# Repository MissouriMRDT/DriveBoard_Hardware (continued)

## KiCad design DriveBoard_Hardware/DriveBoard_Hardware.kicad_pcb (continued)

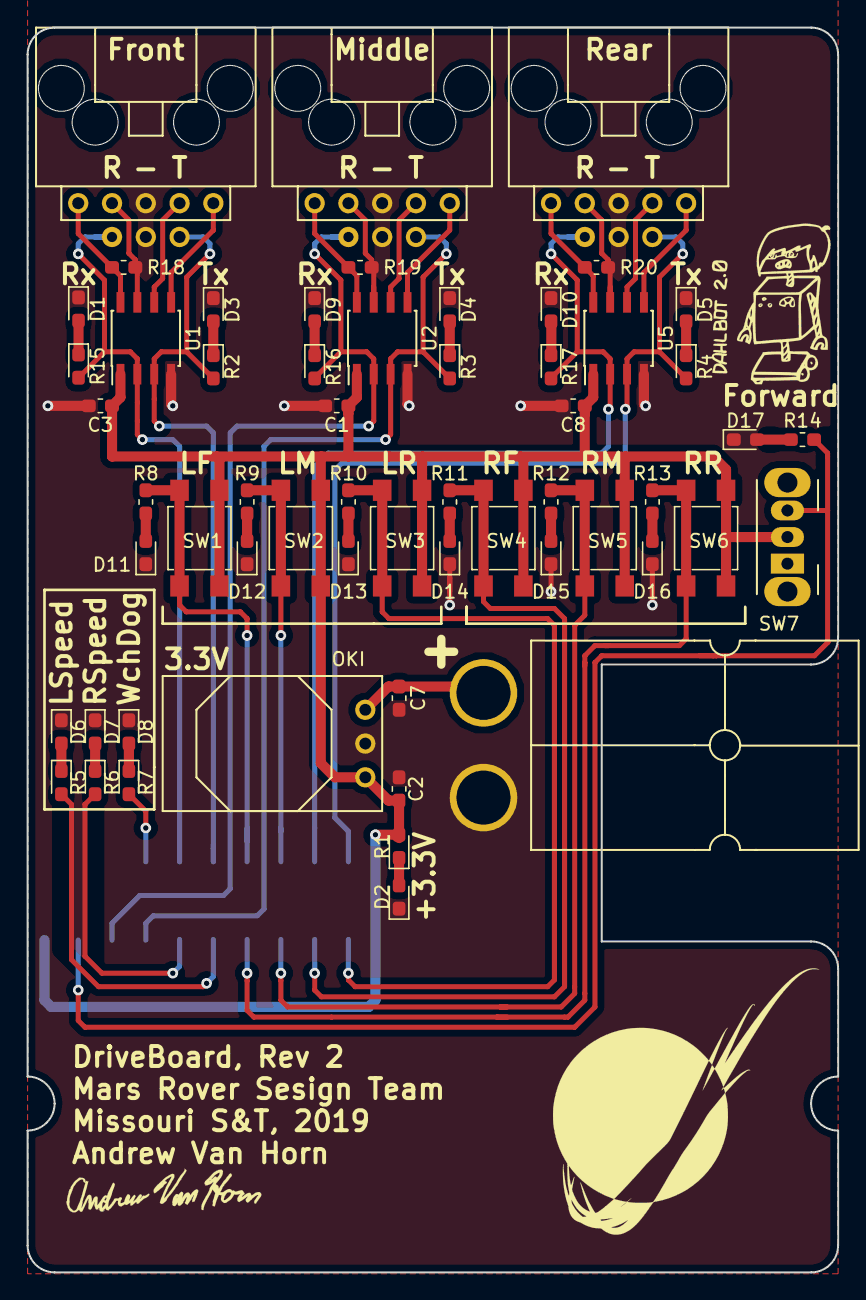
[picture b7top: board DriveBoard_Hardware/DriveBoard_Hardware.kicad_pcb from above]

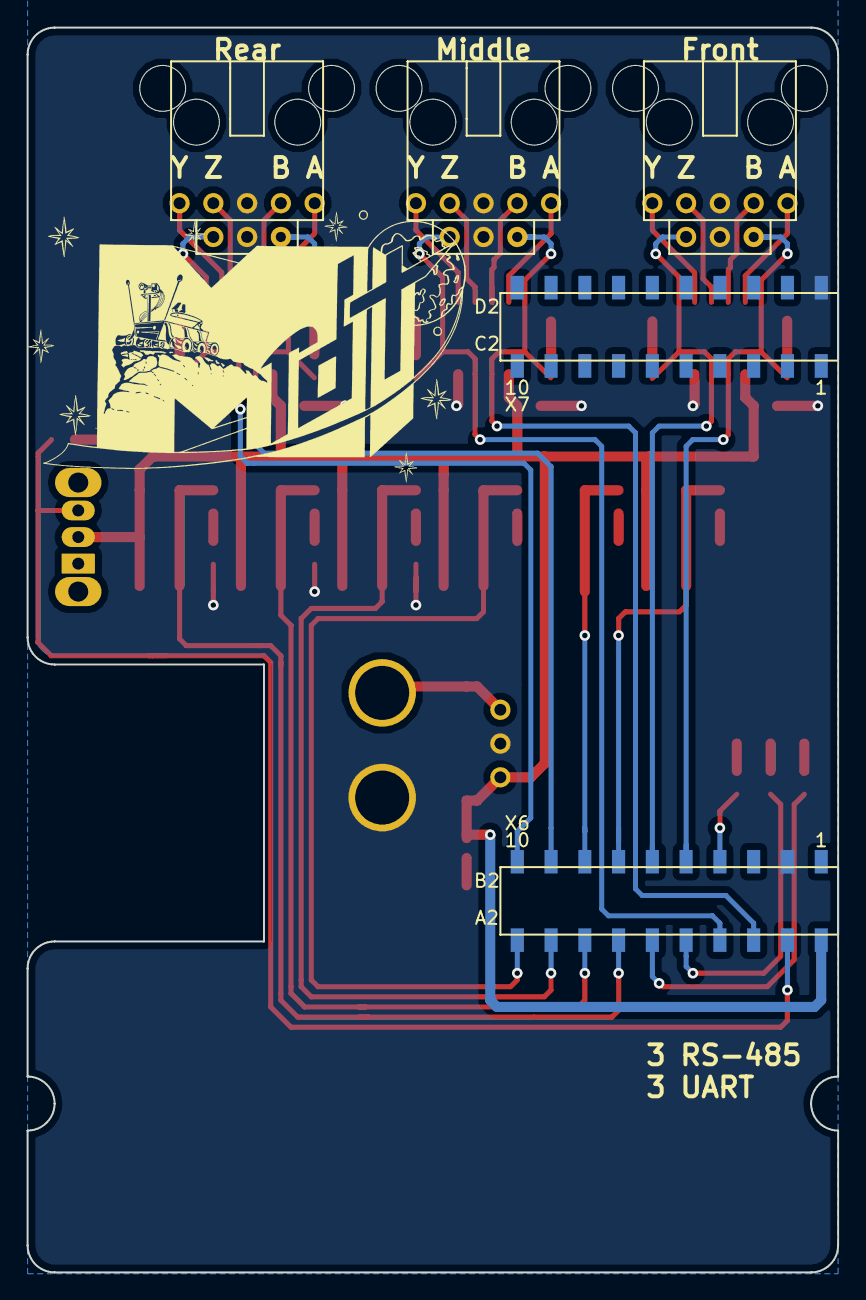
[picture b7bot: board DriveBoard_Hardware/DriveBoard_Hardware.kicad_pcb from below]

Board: 2 copper layers, 61.0 x 93.6 mm, 61 parts (3 on the bottom side), 48 nets.

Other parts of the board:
R18, R19, R20: 120; R_0603_1608Metric_Pad1.05x0.95mm_HandSolder

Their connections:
A1: R18.1; also elsewhere on the board
A2: R19.1; also elsewhere on the board
A3: R20.1; also elsewhere on the board
B1: R18.2; also elsewhere on the board
B2: R19.2; also elsewhere on the board
B3: R20.2; also elsewhere on the board

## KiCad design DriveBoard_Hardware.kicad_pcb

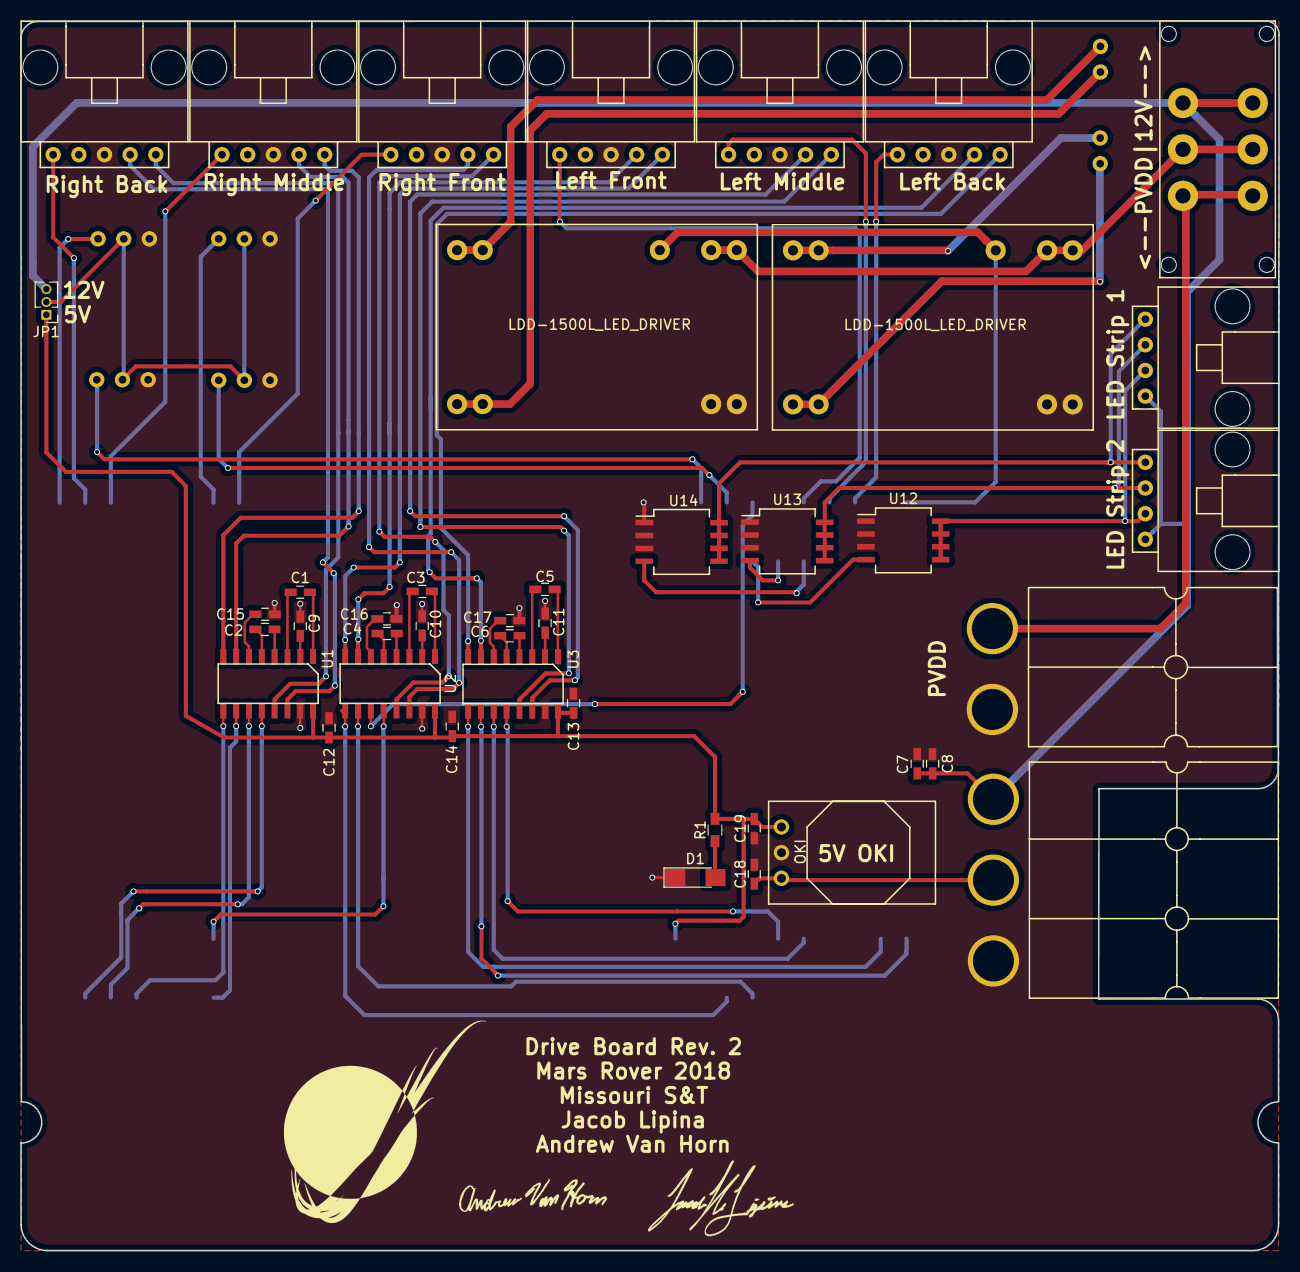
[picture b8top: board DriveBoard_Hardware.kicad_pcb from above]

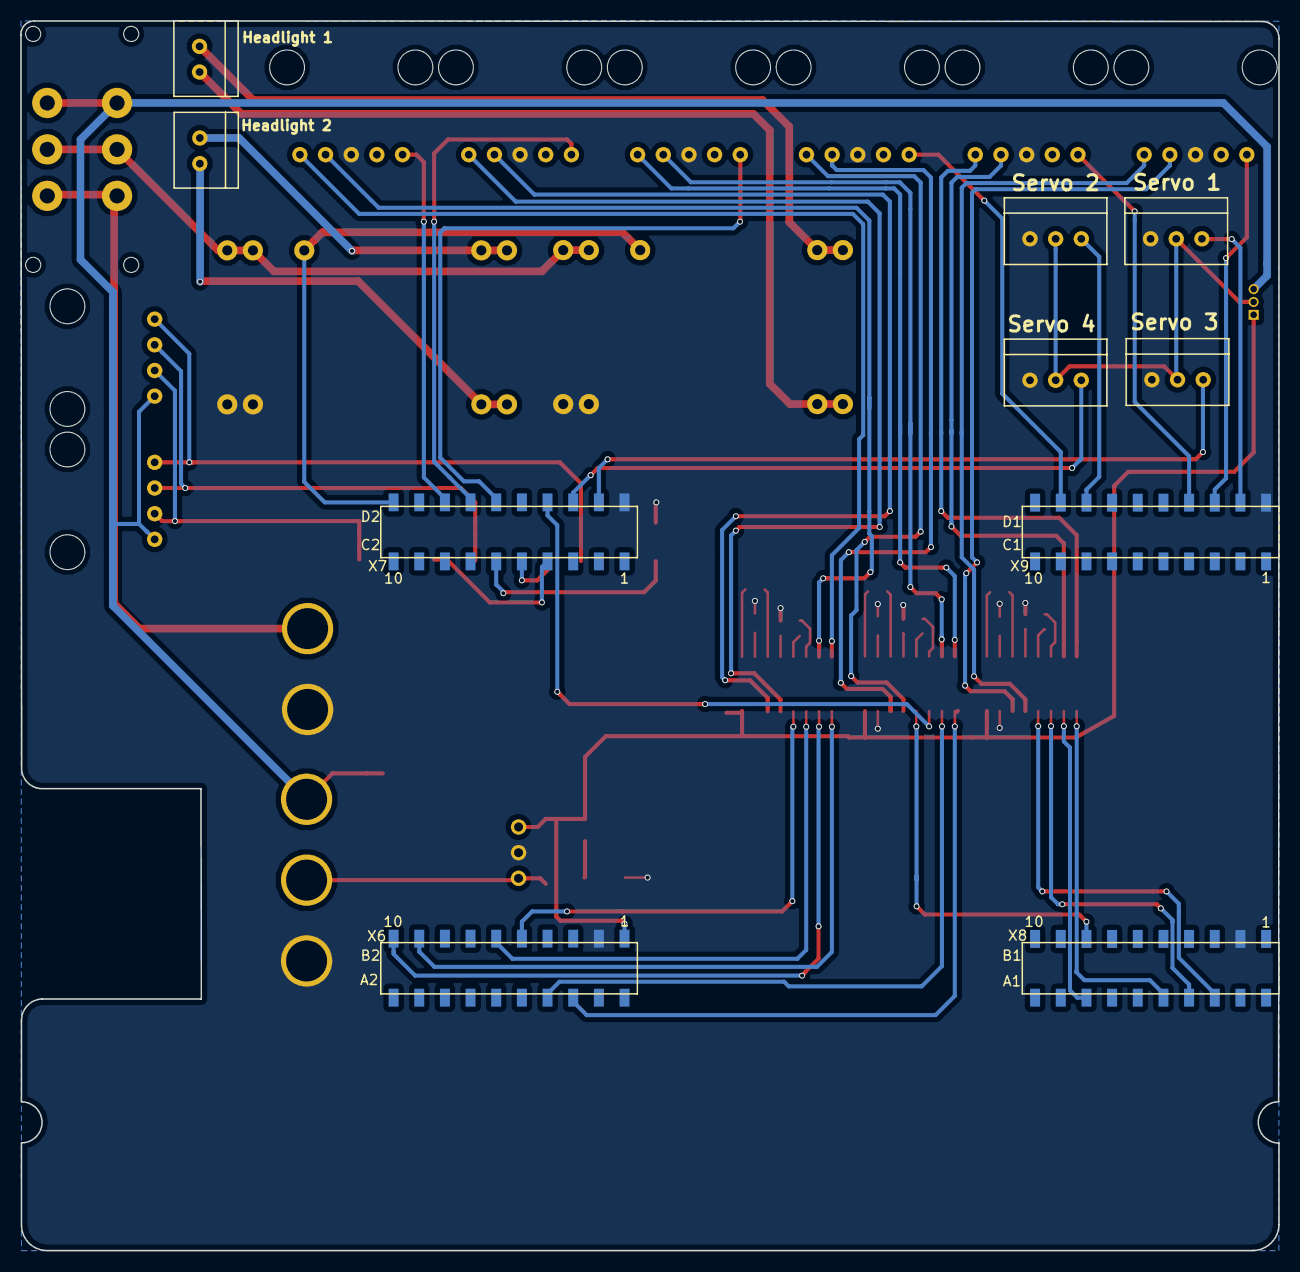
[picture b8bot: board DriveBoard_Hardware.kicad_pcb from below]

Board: 2 copper layers, 124.5 x 121.7 mm, 49 parts (6 on the bottom side), 71 nets.

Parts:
C1, C2, C3, C4, C5, C6, C9, C10, C11, C12, C13, C14, C15, C16, C17: 1u; C_0603_HandSoldering
C7, C8, C18, C19: 10u; C_0603_HandSoldering
C20: Anderson_3; Anderson_3_Horisontal_Side_by_Side
C21: Anderson_2; Anderson_2_Horisontal_Side_by_Side
D1: LED; LED_1206_HandSoldering
JP1: Jumper_NC_Dual; Pin_Header_Straight_1x03_Pitch1.27mm
R1: 500; R_0603_HandSoldering
SW1: SW_DPDT_x2; 1P2T_Angled_Slide_GPI-152-3013
U1, U2, U3: MAX_3232; SOIC_16_3.9x9.9mm_Pitch1.27mm
U4: OKI; OKI_Horisontal
U5: Right Back; MOLEX_SL_5_Horizontal
U6: Right Middle; MOLEX_SL_5_Horizontal
U7: Right Front; MOLEX_SL_5_Horizontal
U8: Left Front; MOLEX_SL_5_Horizontal
U9: Left Middle; MOLEX_SL_5_Horizontal
U10: Left Back; MOLEX_SL_5_Horizontal
U11: TM4C129E_Launchpad_Full; TM4C129E_Launchpad_FULL_Booster_Bottom_SMD
U12, U13, U14: IRF7821PbF; SO-8_5.3x6.2mm_Pitch1.27mm
U15: Strip_1; MOLEX_SL_4_Horizontal
U16: Strip_2; MOLEX_SL_4_Horizontal
U17: Servo_1; MOLEX_SL_3_Vertical
U18: Servo_2; MOLEX_SL_3_Vertical
U19: Servo_3; MOLEX_SL_3_Vertical
U20: Servo_4; MOLEX_SL_3_Vertical
U21, U22: LDD-1500L_LED_DRIVER
U23: Headlight_1; MOLEX_SL_2_Vertical
U24: Headlight_2; MOLEX_SL_2_Vertical

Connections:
12V_Log: C18.2, C20.2, U4.1
+5V: C12.2, C13.2, C14.2, C19.2, JP1.1, R1.2, U1.16, U2.16, U3.16, U4.3, U11.+5V
+12V: C7.2, C8.2, C20.3, JP1.3, SW1.1, U15.4, U16.4
BLUE: U14.5, U14.6, U14.7, U14.8, U15.1, U16.1
BLUE_SIG: U11.PM2, U14.4
DRIVE_PWM_LB: U10.1, U11.PP3
DRIVE_PWM_LF: U8.1, U11.PQ2
DRIVE_PWM_LM: U9.1, U11.PQ3
DRIVE_PWM_RB: U5.1, U11.PH2
DRIVE_PWM_RF: U7.1, U11.PN3
DRIVE_PWM_RM: U6.1, U11.PH3
DRIVE_RX_LB: U3.9, U11.PA4
DRIVE_RX_LF: U2.9, U11.PP0
DRIVE_RX_LM: U3.12, U11.PK0
DRIVE_RX_RB: U1.12, U11.PC4
DRIVE_RX_RF: U2.12, U11.PA6
DRIVE_RX_RM: U1.9, U11.PC6
DRIVE_TX_LB: U3.10, U11.PA5
DRIVE_TX_LF: U2.10, U11.PP1
DRIVE_TX_LM: U3.11, U11.PK1
DRIVE_TX_RB: U1.11, U11.PC5
DRIVE_TX_RF: U2.11, U11.PA7
DRIVE_TX_RM: U1.10, U11.PC7
GND: C7.1, C8.1, C9.2, C10.2, C11.2, C12.1, C13.1, C14.1, C15.2, C16.2, C17.2, C18.1, C19.1, C20.1, C21.2, D1.1, U1.15, U2.15, U3.15, U4.2, U5.3, U6.3, U7.3, U8.3, U9.3, U10.3, U11.GND, U12.1, U12.2, U12.3, U13.1, U13.2, U13.3, U14.1, U14.2, U14.3, U17.1, U18.1, U19.1, U20.1, U21.1, U21.2, U22.1, U22.2
GREEN: U13.5, U13.6, U13.7, U13.8, U15.2, U16.2
GREEN_SIG: U11.PM1, U13.4
HEADLIGHT_CNTR: U11.PM6, U21.21, U22.21
HEADLIGHT_PWR: SW1.2, U21.23, U21.24, U22.23, U22.24
unnamed: C1.1, U1.3
unnamed: C1.2, U1.1
unnamed: C2.1, U1.5
unnamed: C2.2, U1.4
unnamed: C3.1, U2.3
unnamed: C3.2, U2.1
unnamed: C4.1, U2.5
unnamed: C4.2, U2.4
unnamed: C5.1, U3.3
unnamed: C5.2, U3.1
unnamed: C6.1, U3.5
unnamed: C6.2, U3.4
unnamed: C9.1, U1.2
unnamed: C10.1, U2.2
unnamed: C11.1, U3.2
unnamed: C15.1, U1.6
unnamed: C16.1, U2.6
unnamed: C17.1, U3.6
unnamed: D1.2, R1.1
unnamed: JP1.2, U17.2, U18.2, U19.2, U20.2
unnamed: U1.7, U6.4
unnamed: U1.8, U6.5
unnamed: U1.13, U5.5
unnamed: U1.14, U5.4
unnamed: U2.7, U8.4
unnamed: U2.8, U8.5
unnamed: U2.13, U7.5
unnamed: U2.14, U7.4
unnamed: U3.13, U9.5
unnamed: U3.14, U9.4
unnamed: U3.7, U10.4
unnamed: U3.8, U10.5
unnamed: U21.11, U21.12, U23.2
unnamed: U21.13, U21.14, U23.1
unnamed: U22.11, U22.12, U24.2
unnamed: U22.13, U22.14, U24.1
PVDD: C21.1, SW1.3
RED: U12.5, U12.6, U12.7, U12.8, U15.3, U16.3
RED_SIG: U11.PM0, U12.4
SERVO_1: U11.PM3, U17.3
SERVO_2: U11.PN2, U18.3
SERVO_3: U11.PM7, U19.3
SERVO_4: U11.PP5, U20.3

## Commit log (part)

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2015-11-12 added .gitignore
    copied from RoboticArm-Hardware
2015-11-13 created schematic, started board placement and routing
2015-11-13 i think i'm finished with rev 1. Finished placement and routing.
    Placed MAX3077, res's, caps, and rj45's for each motor. Routed all
    power, pwm, and uarts.
2015-11-13 updated library to reflect movement of tiva header pin number labels
2015-11-14 REV 1 FINAL VERSION
    This is the final version of rev 1, however, after a talk with Ethan
    Wilhelm, the form factor does not best match that desired for
    integration into the frame. This version also did not allow mounting due
    to spacing above the 1294's RJ45 jack.
2015-11-15 Finished REV 2?
    I just power through and finished rev 2 I think..
2015-11-17 added hole device, removed unnecessary hole layers
2016-01-11 swapped power input conn from screw terminal to molex 3pin
2016-01-11 repositioned logo
2016-01-11 swapped max3077 component for same in diff lib, changed some lib parts and updated
2016-01-12 changed rj45 conn
2016-01-12 finalized board
2016-01-12 added gerbers
2016-01-20 finished rs232 drive board
2016-01-20 okay nvm not finalized... almost used a IEA232 xcvr... need to use the added rs232 xcvr
2016-01-21 final rs232 version
2016-01-21 changed traces to 12 mil, need to check out L-reconfig before ordering
2016-02-01 fixed wrong width on segment of wire - need to update APP and send off!
2016-02-01 reorganized, need to add in rev1 from older branch
2016-02-02 adjusted board dims, regen'ed gerbers
2016-03-18 updated roboteq profiles
    Both SBL1360s and MBL1660s take the master_clspd profile. Be sure to
    ensure the right polarity of the Number of Poles parameter - it varies
    for each motor.
2016-10-11 Replaced RJ45 Connectors with 15-Pin D-Subs
2016-10-21 Updated connectors and UART hardware
    - Replaced DSubs with Molex-SL 5-pin Connectors
    - Swapped MAX3232 for MAX3078
2016-10-22 Deleted unnecessary folders within the repository
    - Deleted a temp folder made to store exported parts that were not yet
    in the EAGLE-Libraries-Hardware repository
    - Deleted "moco_profiles" folder since it applied to the previous motor
    controllers.
2016-10-23 Changed named wire for 3V3 to supply symbol
2016-10-23 Switched vertical power connector for horizontal.
    APP45_12V_VERT_CONFIG switched to APP45_12V_HORIZ_CONFIG
2016-10-27 Updated board label
    Added my name and the year
2016-10-27 updated gitignore for newer versions of Eagle and removed unnecessary files
2016-10-28 Made slight changes to prepare for board review
    - Added decoupling capacitors to OKI
    - Replaced VCC supply symbol with +5V
    - Disconnected +5V from capacitors (let them connect to +5V plane)
    - Swap connectors 3 and 4 to create progression from right to left
2016-11-07 Flipped the silkscreen for the 5Pin SLs
2016-11-07 Adjusted positions of several board components
    - Repositioned OKI to allow for more room
    - Shifted the two leftmost MAX232s to the left
    - Shifted SL Connectors to be evenly spaced between MAX232s
2016-11-07 Moved silkscreen labels
2016-12-12 Changed serial pairs to match Tiva hardware
2016-12-13 Fixed RS232 chip capacitors
    Several capacitors were going to Vcc when they should have been going to
    Gnd
2016-12-13 Began routing traces
2017-01-31 Routed PWM traces and added power indicator led
2017-01-31 Prep for Board Review
    - Labeled schematic with corresponding Serial channels (from hardware
    serial on Tiva.
    - Added Power Indicator LED and Debug LED
    - Still need to decide on current limiting resistors for LEDs
2017-02-02 Adjusted labels and removed top +5V plane
2017-02-02 Finished routing
2017-02-04 Changes from 2nd Review
    - changed led direction
    - changes led schematic
    - moved vias above max232
    - thickened 12v line
2017-11-10 Modified 2017 Drive Board for BOD 2018
    -Switched all vertical SL connectors to horizontal connectors.
    -Moved horizontal connectors to top of board so that there are only
    connectors on the top and right side of the board.
    -Extended the bottom of the board out further by ~0.6 inches in order to
    place .08 inch diameter mounting holes.
    -Moved ICs and other passives connected to vertical SL connectors
2018-03-26 Created new project in KiCad
    Designing Drive Board Rev.2 2018 in KiCad. Farewell EAGLE.
2018-03-26 Added Power Circuitry in Schematic
2018-03-26 Drive Serial Added
2018-03-26 Added Servos
2018-04-09 Schematic complete and txt file added
2018-04-13 Created full board
2018-04-16 Finished Board Layout
2018-05-03 Fixed Tiva Footprint
2018-05-13 changed header footprint from 1.27mm to 2.54mm
2018-10-13 Cleared Repo
2018-10-16 Cleaned up, organized, and labeled schematic components
2018-10-20 Assigned packages and created layout
2018-10-21 Made pcb layout
2018-10-23 Updated silkscreens
2018-10-25 Revised molex pins and created pin layout and connections txt files
2018-10-25 Revised and organized txt documentation files
2018-11-03 Added traces to pcb layout
2018-11-11 Updated some connections
2018-11-11 Updated molex pins
2018-11-29 Changing to AP1509
2018-11-30 Updated schematic
2018-12-02 First board review revisions txt file
2018-12-04 Updated to using buttons/switch
2018-12-14 changes to schematic and starting changes to layout
2018-12-15 making changes
2018-12-15 finishing changes
2018-12-16 changed BOM
2018-12-16 updating changes (Rev1 Review)
2018-12-16 Updated board review revision progress
2019-03-03 Created rev 2
2019-03-03 Finished BOM
2019-03-03 board review
2019-09-30 begin rough schematic
2019-10-05 Update DriveBoard2020.sch-bak
2019-10-05 Tiva, level shifters, molex
    This reverts commit 14c33bf3896d072e8babb810b236ce765600d1b4.
2019-10-05 organized schematic
2019-10-05 added LED's
2019-10-05 Switches and buttons, forwarded to TIVA
2019-10-07 started assigning footprints
2019-10-07 added capacitors to level shifters, added oki for 5v, finished assigning footprints
2019-10-08 started layout
2019-10-09 fixing bullshit
2019-10-09 tweaked layout
2019-10-09 worked really hard on making layout pretty
2019-11-11 switch level shifters to 3232's
2019-11-15 Added lighting stuff
2019-11-15 assigned some footprints
2019-11-17 worked on integrating lighting and drive board schematic
2019-11-18 minor changes to layout
2019-11-18 working on layout
2019-11-18 finished placing components on layout
2019-11-19 cleaned up repo
2019-11-19 cleaned up schematic some
2019-11-20 edge cuts
2019-11-22 generated step files
2019-12-03 Worked on grids
2019-12-09 added serials and relabled for individual wheel control
2019-12-09 added capacitors to OKI's
2019-12-09 added new switches and indicators
2019-12-09 assigned footprints
2019-12-12 finished schematic
2019-12-12 layout progress
2019-12-12 working on traces
2019-12-12 traces complete
2019-12-12 edgecuts, signatures
2019-12-12 fixed LED and renamed silkscreens
2019-12-12 generated gerbs and step files
2019-12-13 Changes from Review
2019-12-17 re-placed footprints on layout
2019-12-17 more layout changes
2019-12-20 silkscreens and via stitching, corrected some awful traces
2019-12-20 corrected a few more traces
2019-12-21 moved some labels on schematic and redid BOM
2020-01-04 just kidding just a few more things to save from layout
2020-01-07 Fixed gerbs files
2020-01-09 updated pin layout document
2020-09-12 Repo Reorganization
2020-09-14 Added Tiva and Power Connections
2020-09-20 Added Molex connectors, added all serial connections, added LED indicators
2020-09-26 ODrive PWR terminal added
2020-09-26 Added CAN Controller and Transceiver
    Need to verify 16Mhz is correct oscillator for use. Must be parallel cut crystall.
2020-09-26 Fixing CAN Hookup with Transceiver
2020-10-01 Added ODrive Serial, Added LED Indicators, Changed Serial Naming
    Changed serial naming for easier understanding of pinout. Added LED indicators for 5V line, CAN serial, and both ODrive serial connections.
2020-10-05 Absolute Encoder Connections Added
2020-10-08 Added ODrive Data Connectors, Switched schematic page size, removed 12 Logic bus
2020-10-11 Updated LEDs, Organized file layout, removed old files
2020-11-09 Added Footprint for all Components, started board
    Switched ferrite beads to fuses
2020-11-09 Added 12V logic line
2020-11-10 Odrive Pads Updated, Board Outline Finished, Andersons added to board
    12VA pin on anderson symbol was re-assigned to work on pad 2 for 2 port anderson connector.
2020-11-14 All Major Components footprints placed.
    Remaining are resistors, capacitors, and inductors. Silkscreen is also required.
2020-11-15 Added traces for buttons, and moved most resistors and LEDs into position
2020-11-15 All Components in Place. Small amounts of trace work remaining.
2020-11-15 All Components and Traces Placed. Silkscreen Updated.
2020-11-16 Changed Actuation trace width. Added gerbs and BOM to documentation. Added TIVA connections and board connectors text files.
2020-11-17 Switched TIVA SMD bottom to THT. Moved Odrive Andersons and re-traced pwr. Added names to LEDs.
2020-11-23 All Components and Traces Placed
    Finished updating schematic to meet CDR changes.
2020-11-29 Added Gerbs and BOM
2020-11-30 Changed Top plane to GND and routed 3V3 traces.
    Should fix GND islands.
2020-11-30 STEP file fixed, Gerbs Updated, BOM Finished
2020-11-30 Added Digikey Part Number
2020-11-30 gerbs moved to .zip file
2021-09-21 I deleted some 2021 things
2021-09-21 3V3Oki, Tiva, Power LED
2021-09-24 Basically Finished
2021-09-24 I did something guys
2021-09-24 Added Fault LEDs, and Adjusted Placement
2021-09-24 Microfit YASSS~
2021-09-27 Organization for BoardA
2021-10-06 Added 5V OKI, Level Shifters, Organization
2021-10-13 Removed Encoder, Fixed Resistor Values
2021-10-13 Added VESC Connectors, Fixed Switch Resistors
2021-10-21 Changed Switches Back to Buttons; Created Schematic PDF
2021-11-08 6-Pin Molex and Layour from B
2021-11-08 Fix Mislabeled Serial Connections, Serial Traces, GND Vias
2021-11-16 CDR Changes
2021-11-18 Added CDR Alumni Notes
2021-12-08 .STEP file moved to documentation folder
2022-02-20 Finished Schematic and Layout
2022-02-20 Fixed Ethernet Port
2022-02-20 removed the .net exclusion from the gitignore
2022-02-20 Made Traces "Not Ugly"
2022-02-21 BIG Labels
2022-02-22 Board Review Changes
2022-03-10 Changed Buck Converter; Redid Gerbs
2022-03-14 zipped together gerber files
2022-09-15 Driveboard 2023
    New Branch of Driveboard
2022-09-15 Driveboard Rev1 Start
    Teensy, Connectors, Anderson added
2022-09-24 Slight Schematic Change
    Changed the schematic slightly so it wouldn't look too cluttered
2022-09-24 Fixed Changes
    Changed 12V to 36V, same thing with OKI from TSR
    Changed switch to a 2 position switch
    Changed 12V LED to 36V and add 3k Resistor
    Changed all Rx LED to Yellow
2022-09-24 Microfit to SL
    Changed microfits to SL
2022-09-30 Documentation
    Schematic PDF
2022-10-04 Assigned Footprints
    Assigned footprints
2022-10-29 PCB Layout
    Started and Finished Rev1 of DriveBoard
2022-11-03 Layout Review Board
    Finished Changes. Needs to add signatures.
2022-11-03 Added Signature
    Signature added, still need other signatures
2022-11-09 Fixed 1 and 2 Problems from LR
    Increased size of Ground Planes & Ran Traces Away from Ground (Maybe not complete)
2022-11-19 Signature adding and typo correction
    Added my signature and corrected a typo on the board
2022-11-19 Himanth Bobba Signature Added
2022-11-19 Cleaned up board
    Corrected a typo and aligned some texts boxes
2023-03-05 Rev2 Drive Board
    Started Rev2 of Drive Board. Combined Drive Board, Multimedia Board, and Gimbal Board all in one.
2023-03-08 Schematic Review
    Updated connectors, power, notations, pin assignments, and started to construct an Encoder for buttons
2023-03-10 PCB Layout
    Updated the footnotes.
    Started and almost finished the layout.
    Still needs buttons and encoder.
2023-03-15 Added Signature
2023-03-19 Core Board PCB
    Finished Core Board PCB
2023-03-19 Core Board PCB
    Layout Finished
2023-03-19 Core Board PCB
2023-03-21 PCB Layout Core Board
    Finished
2023-03-21 Corrected Capacitor
2023-03-21 generated gerbs and fixed files
2023-04-19 Fixed CoreBoard PCB
    Fixed Pin Assignments
